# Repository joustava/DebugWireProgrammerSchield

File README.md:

# DebugWireDebuggerProgrammerShield

> This repository contains [KiCad](https://www.kicad.org/) designs for an Arduino Nano Shield (atm [THT](https://en.wikipedia.org/wiki/Through-hole_technology)) that can be used as a Programmer and Debugger by using the [DebugWire protocol](https://en.wikipedia.org/wiki/DebugWIRE). It supports several AVR's like ATtiny85. The sketch to enable this is not made by me, it can be found from [wholder/DebugWireDebuggerProgrammer](https://github.com/wholder/DebugWireDebuggerProgrammer).

## Getting started

Once assembled, put the shield on top of a Arduino Nano (assuming you have connectors soldered on the front). Then flash the Arduino Nano with the DebugWireDebuggerProgrammer [sketch](https://github.com/wholder/DebugWireDebuggerProgrammer).

It is now possible to either put a Attiny85 in the socket found on the shield, or to connect to your project by means of a In Circuit Serial Programming (ICSP) connector.

If you use [PlatformIO](https://platformio.org/) you can use the supplied config and src to upload a simple firmware that flashes the IND. LED on the shield.

If you don't, please read through the instructions in [DebugWireDebuggerProgrammerShield.md](./DebugWireDebuggerProgrammerShield.md) for details.

## Note

I am a complete beginner at PCB/Schematics design and *cannot* guarantee that this works. It is a work in progress, a hobby project.
If you do find something odd or plain wrong, feel free to open an issue/contribute and I'll happily try to learn from your wisdom!

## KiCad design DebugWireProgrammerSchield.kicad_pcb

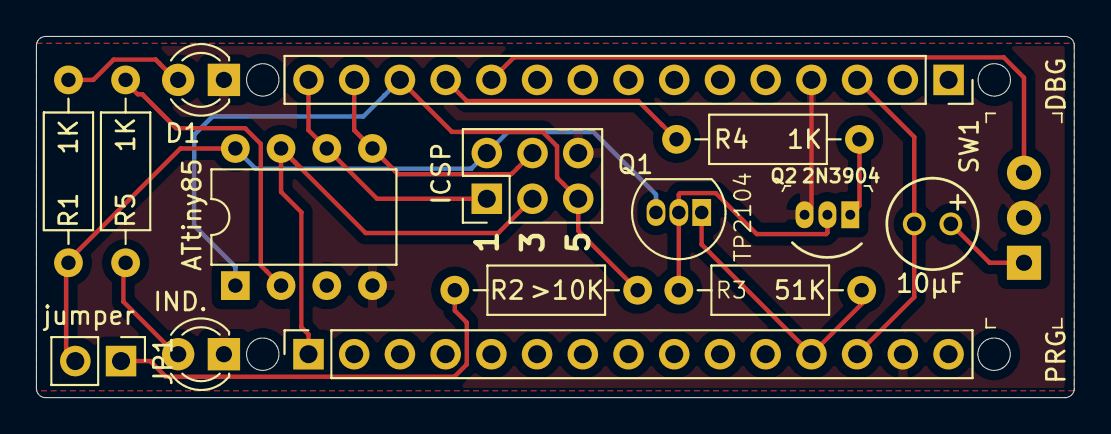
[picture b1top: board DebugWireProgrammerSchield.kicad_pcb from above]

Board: 2 copper layers, 57.7 x 20.1 mm, 16 parts (0 on the bottom side), 17 nets.

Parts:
C1: 10µF; CAP_ELECTRO_D5S2
D1: PWR; LED_D3.0mm
D2: IND.; LED_D3.0mm
J1, J2: Conn_01x15; PinSocket_1x15_P2.54mm_Vertical
J3: ICSP; PinHeader_2x03_P2.54mm_Vertical
JP1: jumper; PinHeader_1x02_P2.54mm_Vertical
Q1: TP2104; TO-92_Inline
Q2: 2N3904; TO-92-3
R1, R4, R5: 1K; R_Axial_DIN0207_L6.3mm_D2.5mm_P10.16mm_Horizontal
R2: >10K; R_Axial_DIN0207_L6.3mm_D2.5mm_P10.16mm_Horizontal
R3: 51K; R_Axial_DIN0207_L6.3mm_D2.5mm_P10.16mm_Horizontal
SW1: PRG/DBG; Switch_Slide_11.6x4mm_EG1218
U1: ATtiny85; DIP-8_W7.62mm

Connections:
/B: Q2.1, R4.1
/C: Q1.2, Q2.2, R3.1
/D: J3.2, JP1.2, Q1.3, R1.1, U1.8
/D8: J1.11, SW1.3
/D9: J1.12, R4.2
/D10: J1.13, J3.5, R2.2, U1.1
/MISO: J1.15, J3.1, U1.6
/MOSI: J1.14, J3.4, U1.5
/PB3(TEST): R5.1, U1.2
/PROG: C1.1, SW1.1
/RST: C1.2, J1.3, J2.13
/S: J2.12, Q1.1, R3.2
/SCK: J2.1, J3.3, U1.7
GND: D1.1, D2.1, J1.4, J2.14, J3.6, Q2.3, SW1.2, U1.4
unnamed: D1.2, R1.2
unnamed: D2.2, R5.2
unnamed: JP1.1, R2.1

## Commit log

2021-02-12 debugwiredebugger-programmer schematics
2021-02-12 create pcb
2021-02-12 update docs
2021-02-12 add note to readme
2021-02-13 cleanup silkscreen typos
